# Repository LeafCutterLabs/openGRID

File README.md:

# openGRID
RGB Silicone Button Pad

PCBs available at https://www.tindie.com/stores/LeafCutter/

keypad.h is the general Arduino library maintained by Mark Stanley and available from Library Manaager

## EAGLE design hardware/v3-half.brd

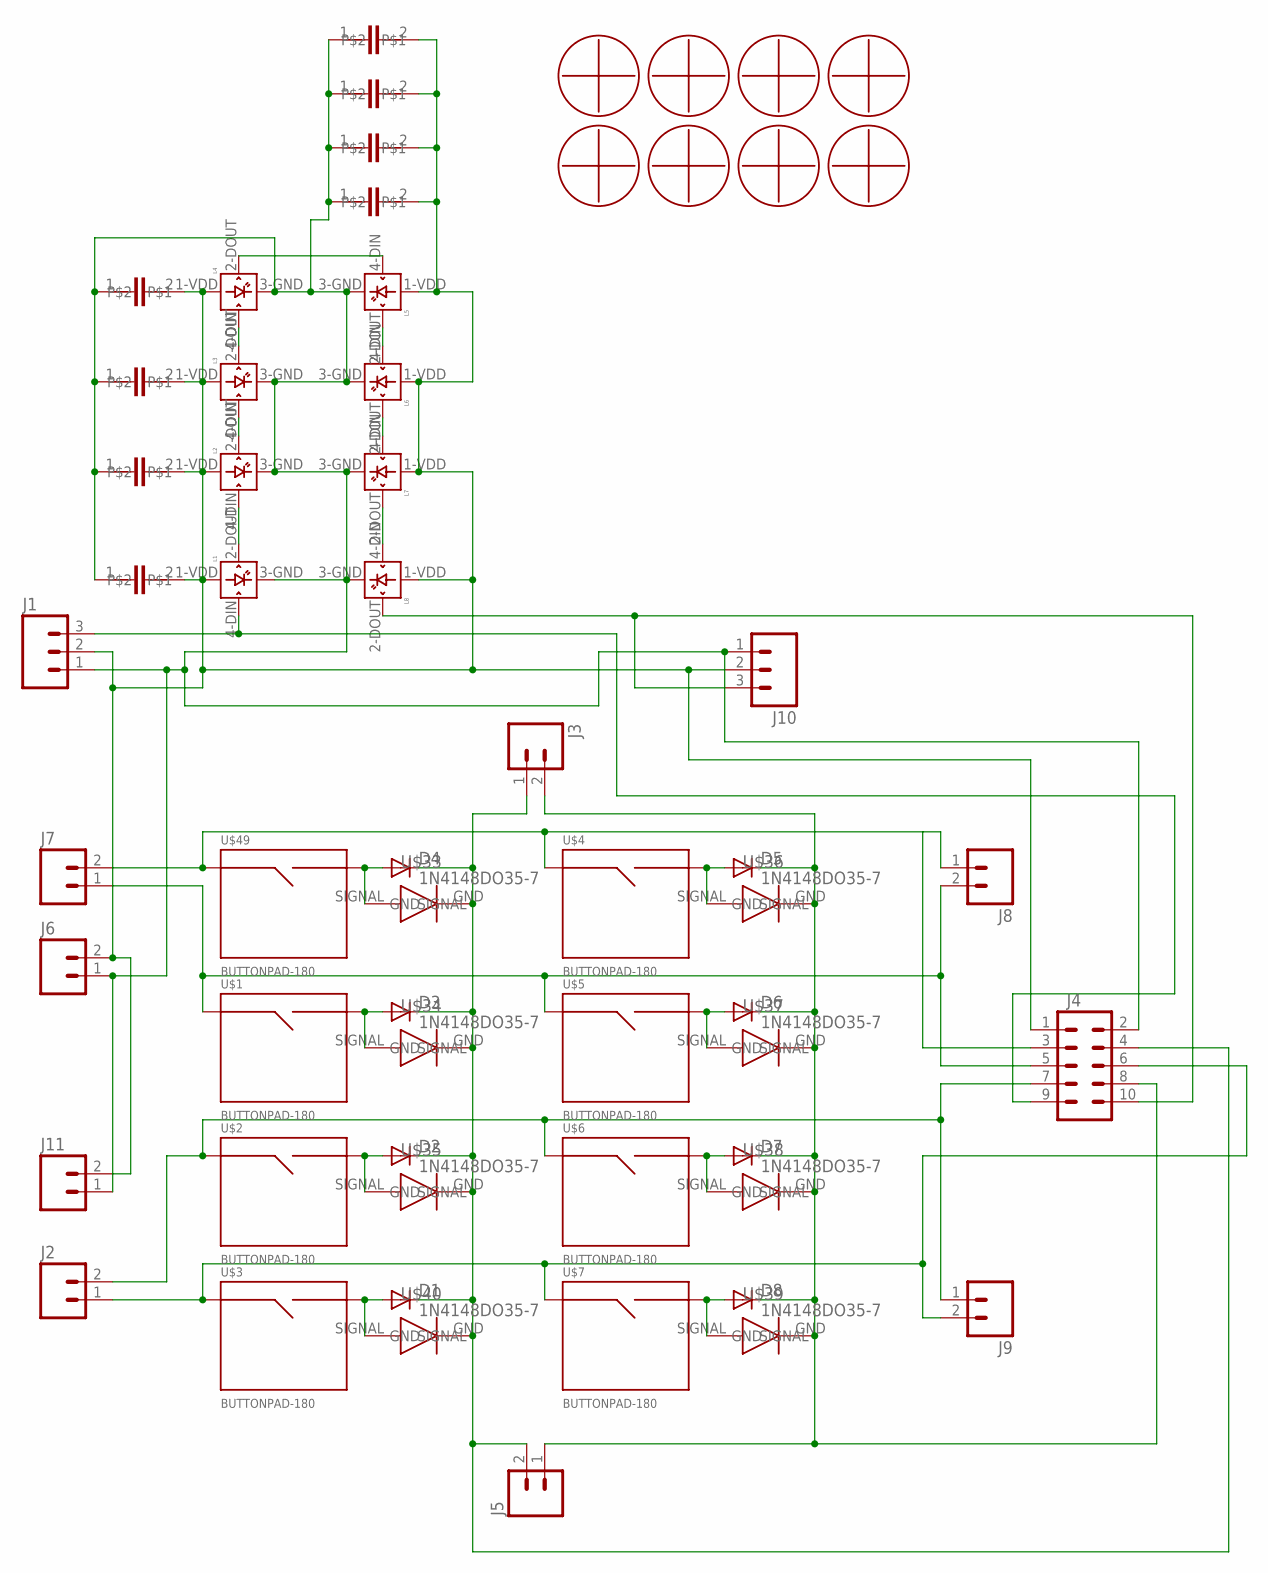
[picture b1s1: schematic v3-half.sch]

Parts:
D1, D2, D3, D4, D5, D6, D7, D8: 1N4148DO35-7; DO35-7
J1, J10: M031X03_NO_SILK; 1X03_NO_SILK
J2, J3, J5, J6, J7, J8, J9, J11: M021X02_NO_SILK; 1X02_NO_SILK
J4: M05X2NO_SILK; 2X5_NOSILK
L1, L2, L3, L4, L5, L6, L7, L8: WS2812B
U$1, U$2, U$3, U$4, U$5, U$6, U$7, U$49: BUTTONPAD-180
U$8, U$9, U$10, U$11, U$12, U$13, U$14, U$15: M25MOUNT
U$17, U$18, U$19, U$20, U$25, U$26, U$27, U$28: 0805CAP; 0805
U$33, U$34, U$35, U$36, U$37, U$38, U$39, U$40: 4148DIODE; SOD-323

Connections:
A: J2.1, J4.6, J9.2, U$3.P$1 (SIG1), U$7.P$1 (SIG1)
B: J2.2, J4.7, J9.1, U$2.P$1 (SIG1), U$6.P$1 (SIG1)
C: J4.5, J7.1, J8.2, U$1.P$1 (SIG1), U$5.P$1 (SIG1)
C1: D1.C, D2.C, D3.C, D4.C, J3.1, J4.4, J5.2, U$33.GND, U$34.GND, U$35.GND, U$40.GND
C2: D5.C, D6.C, D7.C, D8.C, J3.2, J4.8, J5.1, U$36.GND, U$37.GND, U$38.GND, U$39.GND
D: J4.3, J7.2, J8.1, U$4.P$1 (SIG1), U$49.P$1 (SIG1)
DIN: J1.3, J4.9, L1.4-DIN (DIN)
DOUT: J4.10, J10.3, L8.2-DOUT (DOUT)
GND: J1.1, J4.2, J6.1, J10.1, J11.1, L1.3-GND (GND), L2.3-GND (GND), L3.3-GND (GND), L4.3-GND (GND), L5.3-GND (GND), L6.3-GND (GND), L7.3-GND (GND), L8.3-GND (GND), U$17.1, U$18.1, U$19.1, U$20.1, U$25.1, U$26.1, U$27.1, U$28.1
unnamed: D8.A, U$7.P$2 (SIG2), U$39.SIGNAL
unnamed: D7.A, U$6.P$2 (SIG2), U$38.SIGNAL
unnamed: D4.A, U$33.SIGNAL, U$49.P$2 (SIG2)
unnamed: D3.A, U$1.P$2 (SIG2), U$34.SIGNAL
unnamed: D2.A, U$2.P$2 (SIG2), U$35.SIGNAL
unnamed: D1.A, U$3.P$2 (SIG2), U$40.SIGNAL
unnamed: D6.A, U$5.P$2 (SIG2), U$37.SIGNAL
unnamed: D5.A, U$4.P$2 (SIG2), U$36.SIGNAL
unnamed: L1.2-DOUT (DOUT), L2.4-DIN (DIN)
unnamed: L2.2-DOUT (DOUT), L3.4-DIN (DIN)
unnamed: L3.2-DOUT (DOUT), L4.4-DIN (DIN)
unnamed: L4.2-DOUT (DOUT), L5.4-DIN (DIN)
unnamed: L5.2-DOUT (DOUT), L6.4-DIN (DIN)
unnamed: L6.2-DOUT (DOUT), L7.4-DIN (DIN)
unnamed: L7.2-DOUT (DOUT), L8.4-DIN (DIN)
VCC: J1.2, J4.1, J6.2, J10.2, J11.2, L1.1-VDD (VDD), L2.1-VDD (VDD), L3.1-VDD (VDD), L4.1-VDD (VDD), L5.1-VDD (VDD), L6.1-VDD (VDD), L7.1-VDD (VDD), L8.1-VDD (VDD), U$17.2, U$18.2, U$19.2, U$20.2, U$25.2, U$26.2, U$27.2, U$28.2

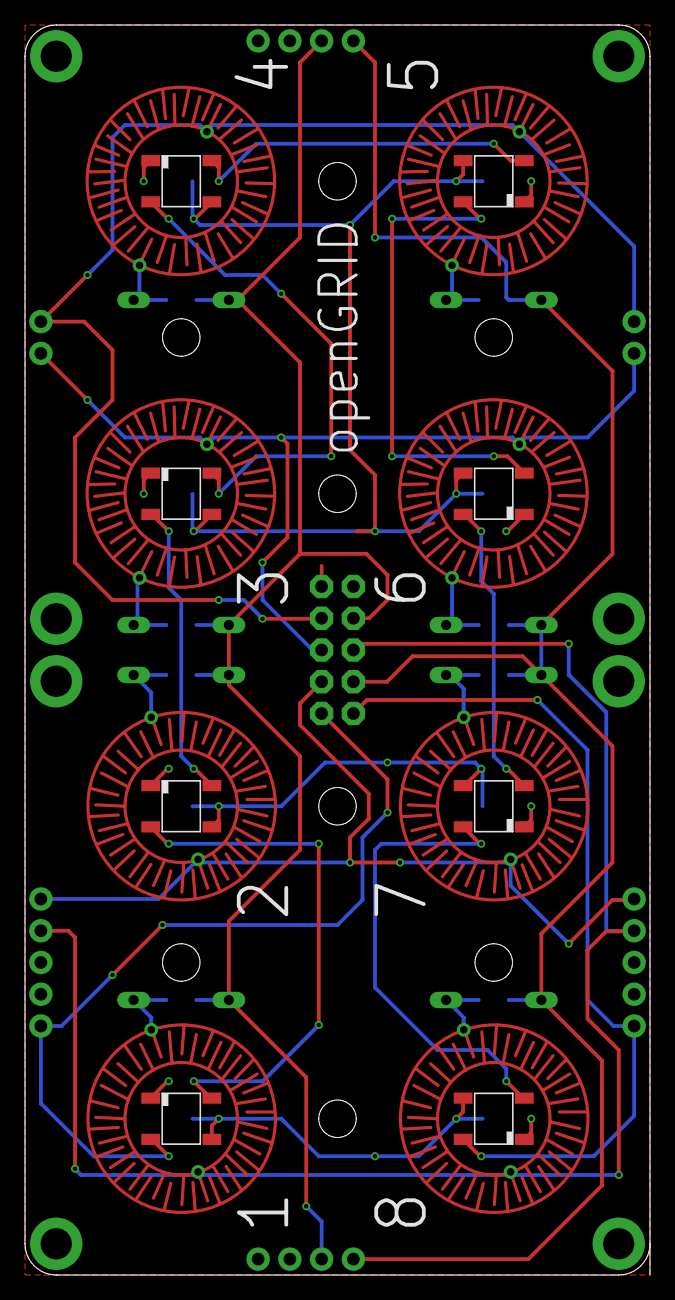
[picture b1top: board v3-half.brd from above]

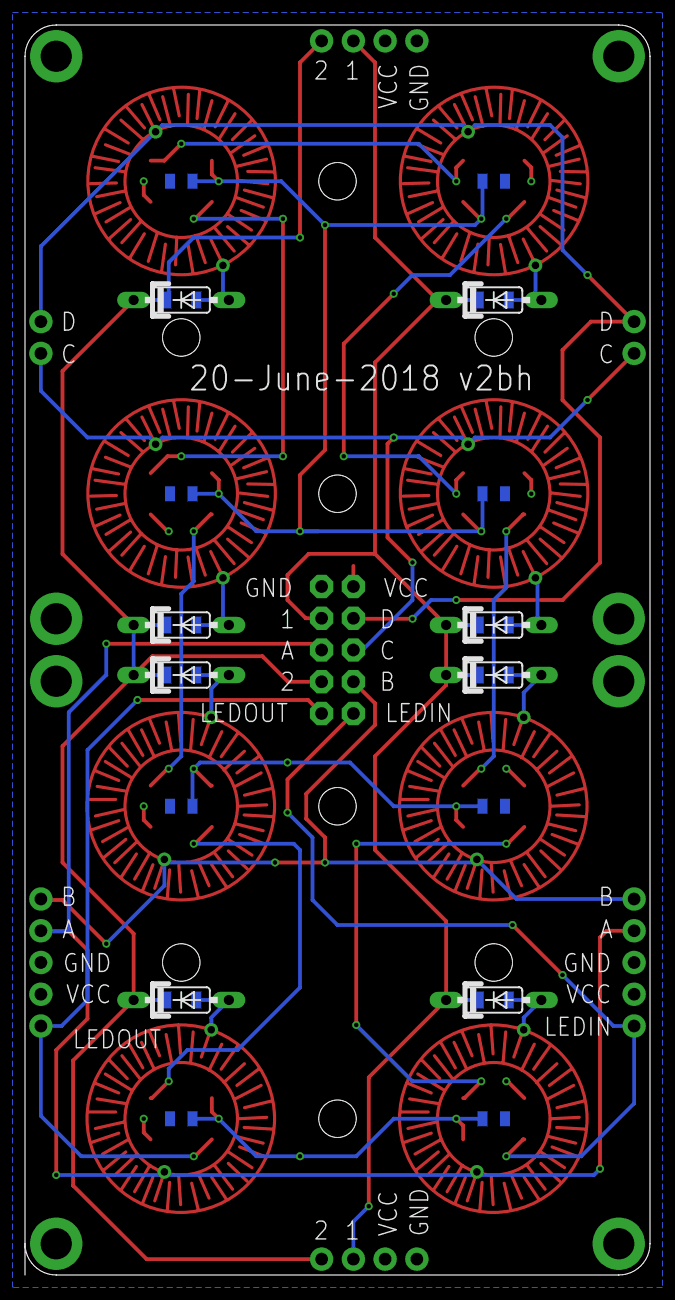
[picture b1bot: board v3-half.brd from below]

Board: 2 copper layers, 50.0 x 100.0 mm, 59 parts (24 on the bottom side), 25 nets.

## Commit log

2018-06-23 Create board-test
2018-06-23 Add files via upload
    Cycles the button through 16 colors, hold the button to turn off
2018-06-23 Create placeholder
2018-06-29 Create info
2018-10-25 Add files via upload
    Step sequencer example

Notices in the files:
parts and their libraries:
SparkFun-Connectors: Licensing: Creative Commons ShareAlike 4.0 International - https://creativecommons.org/licenses/by-sa/4.0
